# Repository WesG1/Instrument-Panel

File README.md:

# Instrument Panel
Description:
    Digital custom 65 mustang modern insturment panel. Uses six servo motors along with RGB LEDs to display gauge information. Controlled by an ESP32-s2. Motors and warning lights are interfaced through I2C protocall using a PCA9685 controller. Odometer and tripmeter are displayed on an I2C LCD. 
    
    Odo and trip values are stored in an EEPROM chip with a wear leveling algorithm. Odometer value is also stored in a second backup EEPROM. At startup the values of both EEPROMs are read, and if they are different the higher value is set as the current mileage. At shutdown the last stored value and current value for the mileage are compared and the current value is only stored if it is higher than the saved value.

    Each servo motor (execpt voltage) has a deticated sensor. The signals from the oil, temp, and fuel sensors are passed through a calibrated voltage divider to drop them to a level safe for the ESP32 to read. Speed and tach are a digital pulse and are passed through a logic shifter. Voltage is derived by an algorithm and read by a voltage divider from the dash power supply. Volts, oil, temp, and fuel have accompanying warning lights that turn red if the value goes out of a safe range, are off if the value is normal and the headlights are off, and white if the values is normal and the headlights are on. Temp has additionally will turn yellow if the value is too low.

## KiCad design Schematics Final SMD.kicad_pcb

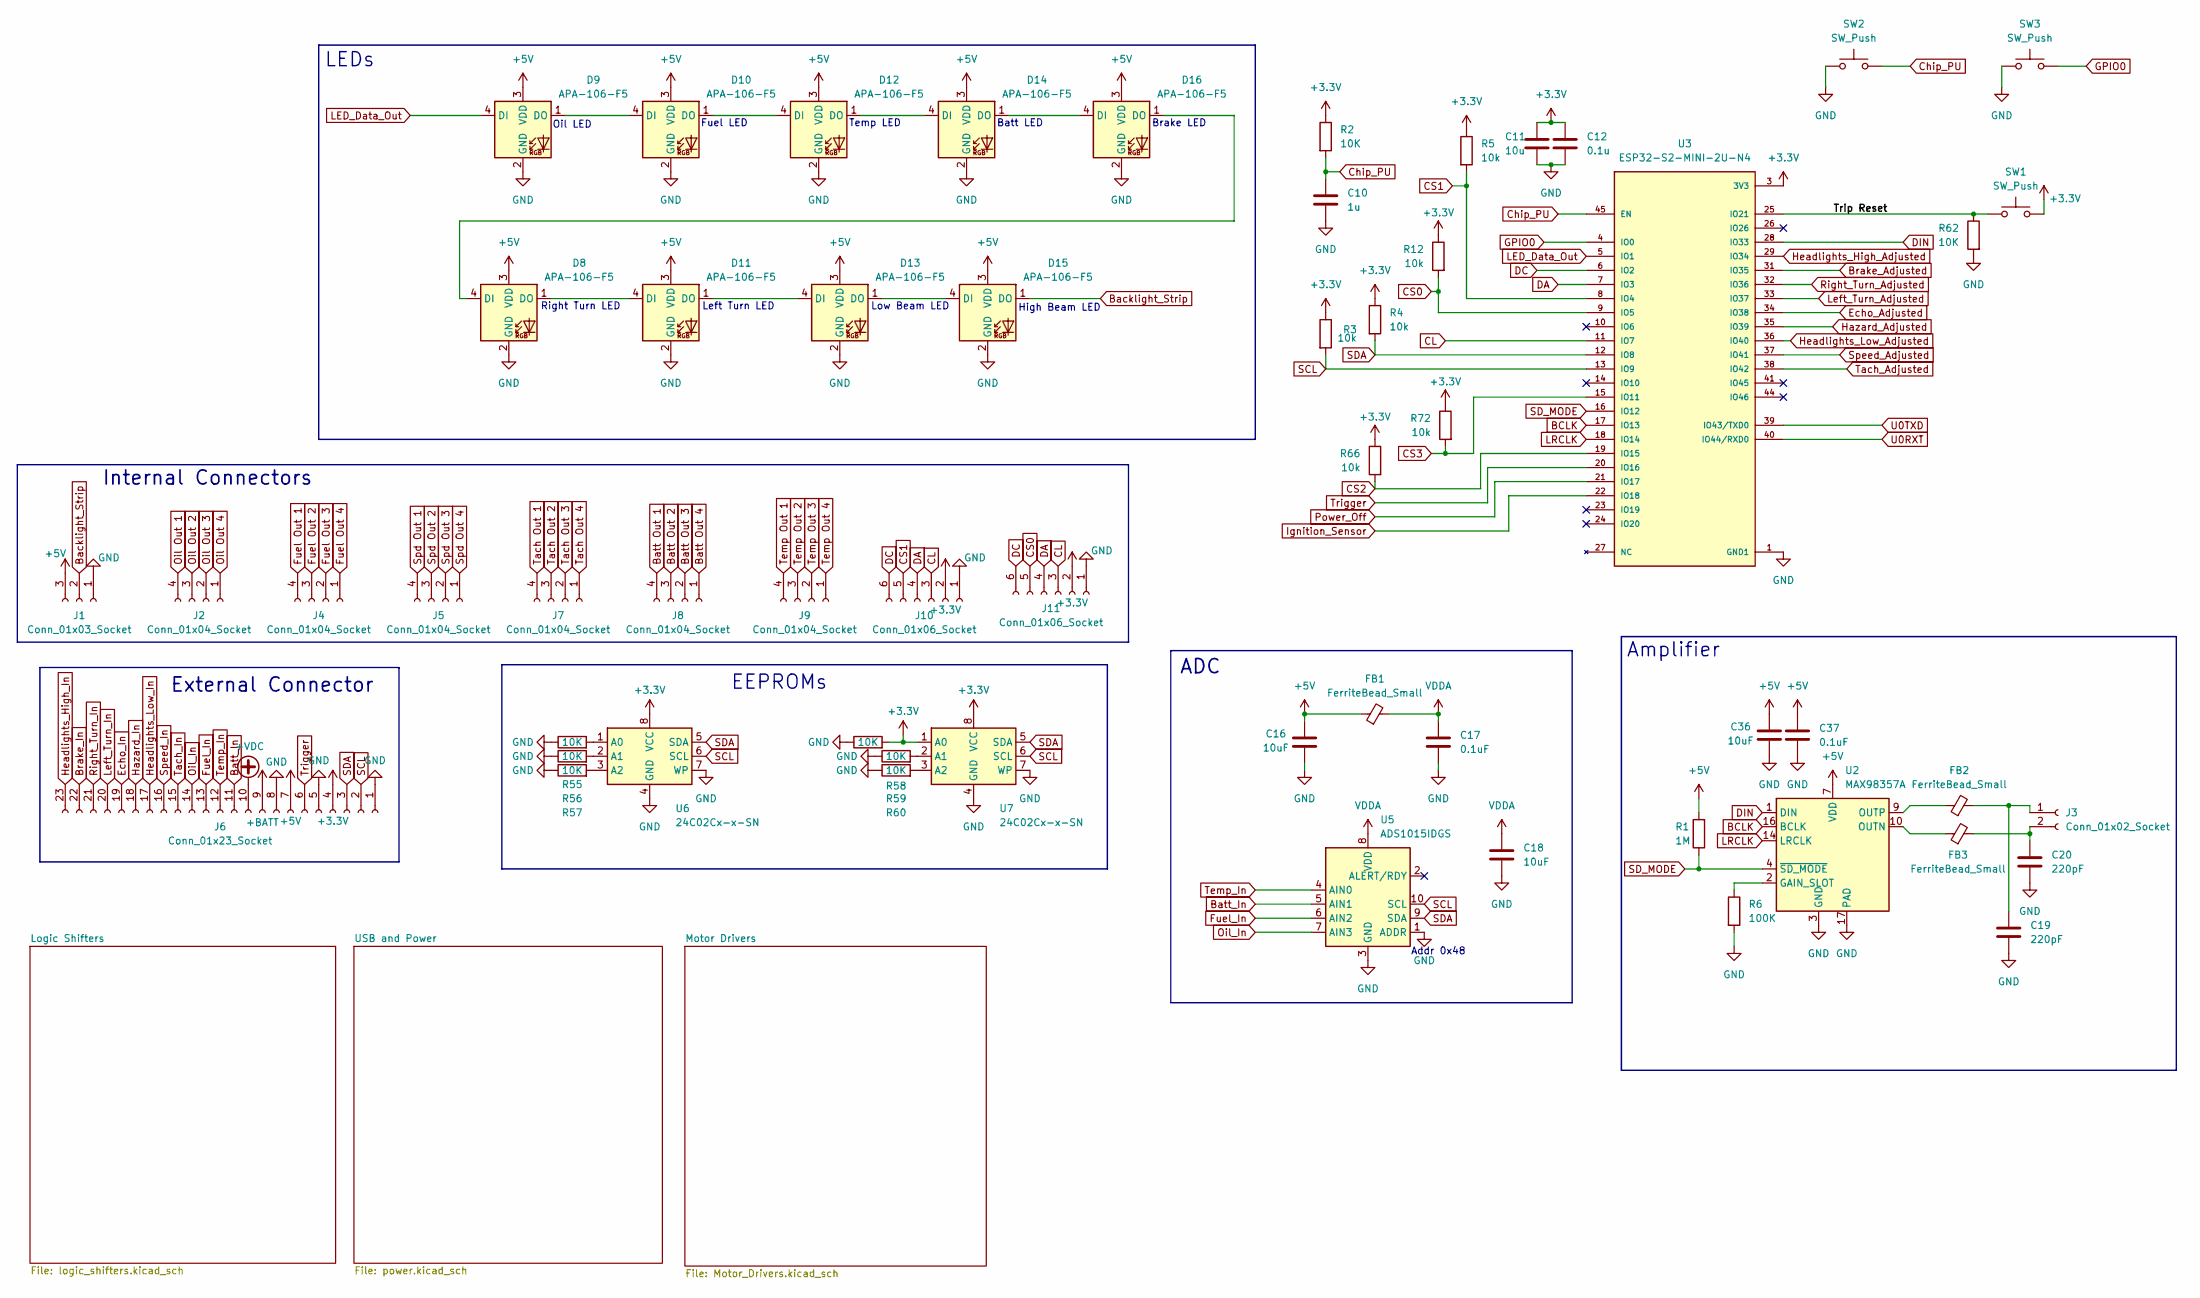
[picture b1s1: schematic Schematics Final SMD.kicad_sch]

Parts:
C10: 1u; C_Disc_D3.0mm_W1.6mm_P2.50mm
C11: 10u; C_Disc_D3.0mm_W1.6mm_P2.50mm
C12: 0.1u; C_Disc_D3.0mm_W1.6mm_P2.50mm
C16, C18, C36: 10uF; C_Disc_D3.0mm_W1.6mm_P2.50mm
C17, C37: 0.1uF; C_Disc_D3.0mm_W1.6mm_P2.50mm
C19, C20: 220pF; C_Disc_D3.0mm_W1.6mm_P2.50mm
D8, D9, D10, D11, D12, D13, D14, D15, D16: APA-106-F5; LED_D5.0mm-4_RGB
FB1, FB2, FB3: FerriteBead_Small; L_Axial_L5.0mm_D3.6mm_P10.00mm_Horizontal_Murata_BL01RN1A2A2
J1: Conn_01x03_Socket; Hirose_DF13-03P-1.25DSA_1x03_P1.25mm_Vertical
J2, J4, J5, J7, J8, J9: Conn_01x04_Socket
J3: Conn_01x02_Socket; Hirose_DF13-02P-1.25DSA_1x02_P1.25mm_Vertical
J6: Conn_01x23_Socket; Molex_SL_171971-0023_1x23_P2.54mm_Vertical
J10, J11: Conn_01x06_Socket; Hirose_DF13-06P-1.25DSA_1x06_P1.25mm_Vertical
R1: 1M; R_Axial_DIN0207_L6.3mm_D2.5mm_P10.16mm_Horizontal
R2, R55, R56, R57, R58, R59, R60, R62: 10K; R_Axial_DIN0207_L6.3mm_D2.5mm_P10.16mm_Horizontal
R3, R4, R5, R12, R66, R72: 10k; R_Axial_DIN0207_L6.3mm_D2.5mm_P10.16mm_Horizontal
R6: 100K; R_Axial_DIN0207_L6.3mm_D2.5mm_P10.16mm_Horizontal
SW1, SW2, SW3: SW_Push; SW_PUSH_6mm_H8mm
U2: MAX98357A; TQFN-16-1EP_3x3mm_P0.5mm_EP1.23x1.23mm
U3: ESP32-S2-MINI-2U-N4; XCVR_ESP32-S2-MINI-2U-N4; PARTREV v0.5
U5: ADS1015IDGS; TSSOP-10_3x3mm_P0.5mm
U6, U7: 24C02Cx-x-SN; DIP-8_W7.62mm

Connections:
+3.3V: C11.1, C12.1, J6.4, J10.2, J11.2, R2.1, R3.1, R4.1, R5.1, R12.1, R58.2, R66.1, R72.1, SW1.1, U3.3 (3V3), U6.8 (VCC), U7.1 (A0), U7.8 (VCC); also elsewhere on the board
+5V: C16.1, C36.1, C37.1, D8.3 (VDD), D9.3 (VDD), D10.3 (VDD), D11.3 (VDD), D12.3 (VDD), D13.3 (VDD), D14.3 (VDD), D15.3 (VDD), D16.3 (VDD), FB1.1, J1.3, J6.7, R1.2, U2.7 (VDD), U2.8 (VDD); also elsewhere on the board
+BATT: J6.9; also elsewhere on the board
+VDC: J6.10; also elsewhere on the board
/Trip Reset: R62.1, SW1.2, U3.25 (IO21)
BCLK: U2.16 (BCLK), U3.17 (IO13)
Backlight_Strip: D15.1 (DO), J1.2
Batt Out 1: J8.4; also elsewhere on the board
Batt Out 2: J8.3; also elsewhere on the board
Batt Out 3: J8.2; also elsewhere on the board
Batt Out 4: J8.1; also elsewhere on the board
Batt_In: J6.11, U5.5 (AIN1)
Brake_In: J6.22; also elsewhere on the board
CL: J10.3, J11.3, U3.11 (IO7); also elsewhere on the board
CS0: J11.5, R12.2, U3.9 (IO5)
CS1: J10.5, R5.2, U3.8 (IO4)
CS2: R66.2, U3.19 (IO15); also elsewhere on the board
CS3: R72.2, U3.15 (IO11); also elsewhere on the board
Chip_PU: C10.1, R2.2, SW2.2, U3.45 (EN); also elsewhere on the board
DA: J10.4, J11.4, U3.7 (IO3); also elsewhere on the board
DC: J10.6, J11.6, U3.6 (IO2)
DIN: U2.1 (DIN), U3.28 (IO33)
Echo_In: J6.19; also elsewhere on the board
Fuel Out 1: J4.4; also elsewhere on the board
Fuel Out 2: J4.3; also elsewhere on the board
Fuel Out 3: J4.2; also elsewhere on the board
Fuel Out 4: J4.1; also elsewhere on the board
Fuel_In: J6.13, U5.6 (AIN2)
GND: C10.2, C11.2, C12.2, C16.2, C17.2, C18.2, C19.2, C20.2, C36.2, C37.2, D8.2 (GND), D9.2 (GND), D10.2 (GND), D11.2 (GND), D12.2 (GND), D13.2 (GND), D14.2 (GND), D15.2 (GND), D16.2 (GND), J1.1, J6.1, J6.5, J6.8, J10.1, J11.1, R6.2, R55.1, R56.1, R57.1, R58.1, R59.1, R60.1, R62.2, SW2.1, SW3.1, U2.3 (GND), U2.11 (GND), U2.15 (GND), U2.17 (PAD), U3.1 (GND1), U3.2 (GND1__1), U3.30 (GND1__2), U3.42 (GND1__3), U3.43 (GND1__4), U3.46 (GND1__5), U3.47 (GND1__6), U3.48 (GND1__7), U3.49 (GND1__8), U3.50 (GND1__9), U3.51 (GND1__10), U3.52 (GND1__11), U3.53 (GND1__12), U3.54 (GND1__13), U3.55 (GND1__14), U3.56 (GND2), U3.57 (GND2__1), U3.58 (GND2__2), U3.59 (GND2__3), U3.60 (GND2__4), U3.61_1 (GND2__5), U3.61_2 (GND2__6), U3.61_3 (GND2__7), U3.61_4 (GND2__8), U3.61_5 (GND2__9), U3.61_6 (GND2__10), U3.61_7 (GND2__11), U3.61_8 (GND2__12), U3.61_9 (GND2__13), U3.62 (GND2__14), U3.63 (GND3), U3.64 (GND3__1), U3.65 (GND3__2), U5.1 (ADDR), U5.3 (GND), U6.4 (GND), U6.7 (WP), U7.4 (GND), U7.7 (WP); also elsewhere on the board
GPIO0: SW3.2, U3.4 (IO0); also elsewhere on the board
Hazard_In: J6.18; also elsewhere on the board
Headlights_High_In: J6.23; also elsewhere on the board
Headlights_Low_In: J6.17; also elsewhere on the board
LED_Data_Out: D9.4 (DI), U3.5 (IO1)
LRCLK: U2.14 (LRCLK), U3.18 (IO14)
Left_Turn_In: J6.20; also elsewhere on the board
unnamed: D9.1 (DO), D10.4 (DI)
unnamed: D10.1 (DO), D12.4 (DI)
unnamed: D8.1 (DO), D11.4 (DI)
unnamed: D11.1 (DO), D13.4 (DI)
unnamed: D12.1 (DO), D14.4 (DI)
unnamed: D13.1 (DO), D15.4 (DI)
unnamed: D14.1 (DO), D16.4 (DI)
unnamed: D8.4 (DI), D16.1 (DO)
unnamed: C19.1, FB2.2, J3.1
unnamed: C20.1, FB3.2, J3.2
unnamed: R6.1, U2.2 (GAIN_SLOT)
unnamed: FB3.1, U2.10 (OUTN)
unnamed: FB2.1, U2.9 (OUTP)
unnamed: R55.2, U6.1 (A0)
unnamed: R56.2, U6.2 (A1)
unnamed: R57.2, U6.3 (A2)
unnamed: R59.2, U7.2 (A1)
unnamed: R60.2, U7.3 (A2)
Oil Out 1: J2.4; also elsewhere on the board
Oil Out 2: J2.3; also elsewhere on the board
Oil Out 3: J2.2; also elsewhere on the board
Oil Out 4: J2.1; also elsewhere on the board
Oil_In: J6.14, U5.7 (AIN3)
Right_Turn_In: J6.21; also elsewhere on the board
SCL: J6.2, R3.2, U3.13 (IO9), U5.10 (SCL), U6.6 (SCL), U7.6 (SCL)
SDA: J6.3, R4.2, U3.12 (IO8), U5.9 (SDA), U6.5 (SDA), U7.5 (SDA)
SD_MODE: R1.1, U2.4 (~SD_MODE), U3.16 (IO12)
Spd Out 1: J5.4; also elsewhere on the board
Spd Out 2: J5.3; also elsewhere on the board
Spd Out 3: J5.2; also elsewhere on the board
Spd Out 4: J5.1; also elsewhere on the board
Speed_In: J6.16; also elsewhere on the board
Tach Out 1: J7.4; also elsewhere on the board
Tach Out 2: J7.3; also elsewhere on the board
Tach Out 3: J7.2; also elsewhere on the board
Tach Out 4: J7.1; also elsewhere on the board
Tach_In: J6.15; also elsewhere on the board
Temp Out 1: J9.4; also elsewhere on the board
Temp Out 2: J9.3; also elsewhere on the board
Temp Out 3: J9.2; also elsewhere on the board
Temp Out 4: J9.1; also elsewhere on the board
Temp_In: J6.12, U5.4 (AIN0)
Trigger: J6.6, U3.20 (IO16)
VDDA: C17.1, C18.1, FB1.2, U5.8 (VDD)

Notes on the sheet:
Batt LED
Low Beam LED
Brake LED
Amplifier
External Connector
Temp LED
Left Turn LED
ADC
High Beam LED
Addr 0x48
EEPROMs
Fuel LED
Internal Connectors
Oil LED
LEDs
Right Turn LED

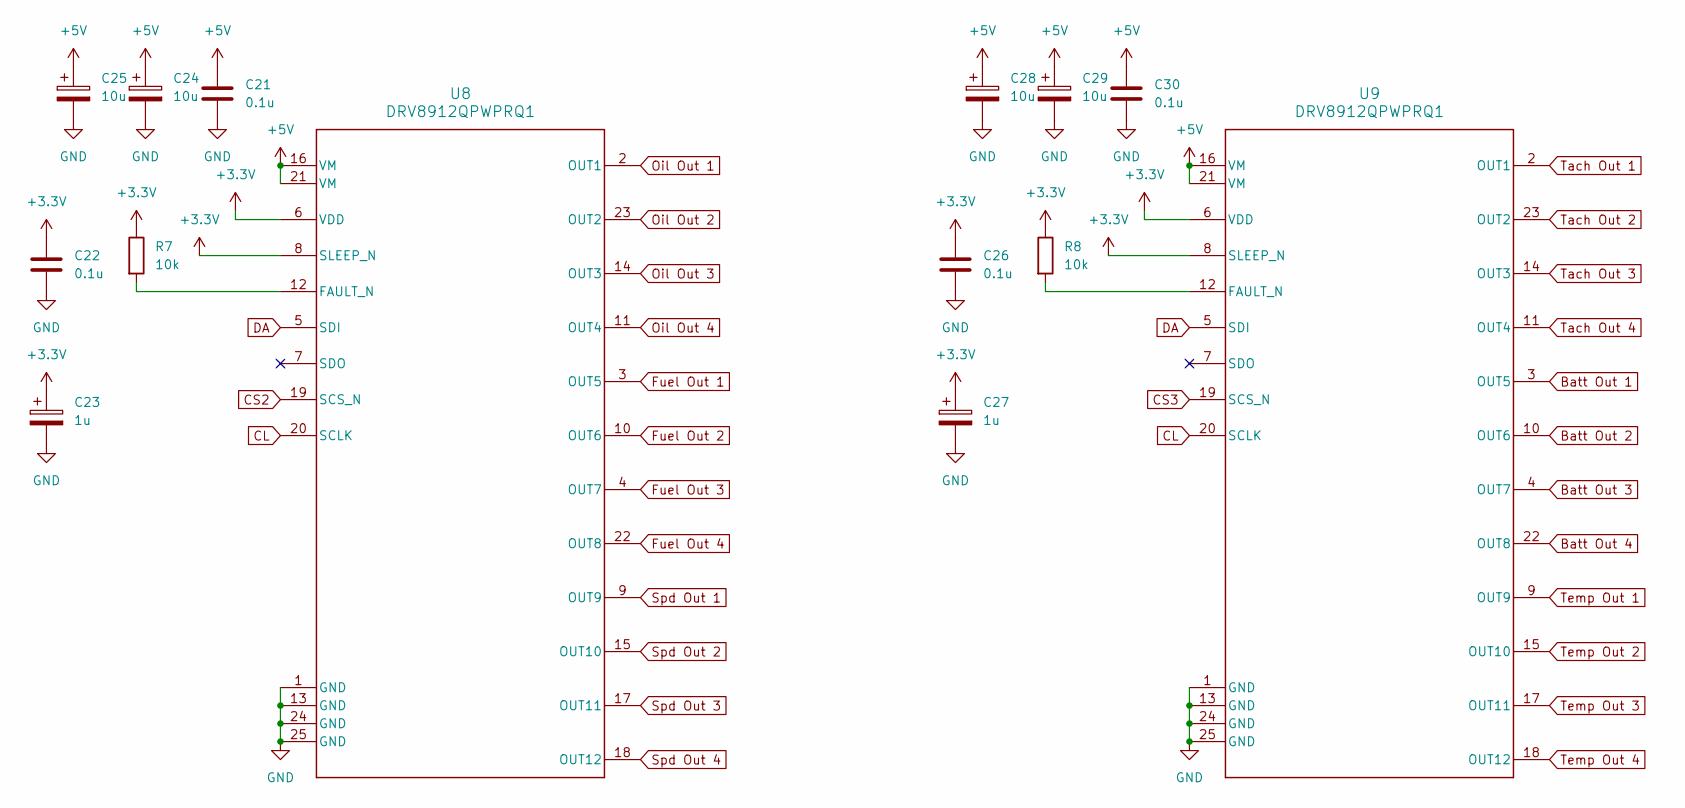
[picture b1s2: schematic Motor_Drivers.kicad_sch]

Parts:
C21, C22, C26, C30: 0.1u; C_1206_3216Metric
C23, C27: 1u; C_1206_3216Metric
C24, C25, C28, C29: 10u; C_1206_3216Metric
R7, R8: 10k; R_1206_3216Metric
U8, U9: DRV8912QPWPRQ1; PWP0024N_N

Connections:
+3.3V: C22.1, C23.1, C26.1, C27.1, R7.1, R8.1, U8.6 (VDD), U8.8 (SLEEP_N), U9.6 (VDD), U9.8 (SLEEP_N); also elsewhere on the board
+5V: C21.1, C24.1, C25.1, C28.1, C29.1, C30.1, U8.16 (VM), U8.21 (VM), U9.16 (VM), U9.21 (VM); also elsewhere on the board
Batt Out 1: U9.3 (OUT5); also elsewhere on the board
Batt Out 2: U9.10 (OUT6); also elsewhere on the board
Batt Out 3: U9.4 (OUT7); also elsewhere on the board
Batt Out 4: U9.22 (OUT8); also elsewhere on the board
CL: U8.20 (SCLK), U9.20 (SCLK); also elsewhere on the board
CS2: U8.19 (SCS_N); also elsewhere on the board
CS3: U9.19 (SCS_N); also elsewhere on the board
DA: U8.5 (SDI), U9.5 (SDI); also elsewhere on the board
Fuel Out 1: U8.3 (OUT5); also elsewhere on the board
Fuel Out 2: U8.10 (OUT6); also elsewhere on the board
Fuel Out 3: U8.4 (OUT7); also elsewhere on the board
Fuel Out 4: U8.22 (OUT8); also elsewhere on the board
GND: C21.2, C22.2, C23.2, C24.2, C25.2, C26.2, C27.2, C28.2, C29.2, C30.2, U8.1 (GND), U8.13 (GND), U8.24 (GND), U8.25 (GND), U9.1 (GND), U9.13 (GND), U9.24 (GND), U9.25 (GND); also elsewhere on the board
unnamed: R7.2, U8.12 (FAULT_N)
unnamed: R8.2, U9.12 (FAULT_N)
Oil Out 1: U8.2 (OUT1); also elsewhere on the board
Oil Out 2: U8.23 (OUT2); also elsewhere on the board
Oil Out 3: U8.14 (OUT3); also elsewhere on the board
Oil Out 4: U8.11 (OUT4); also elsewhere on the board
Spd Out 1: U8.9 (OUT9); also elsewhere on the board
Spd Out 2: U8.15 (OUT10); also elsewhere on the board
Spd Out 3: U8.17 (OUT11); also elsewhere on the board
Spd Out 4: U8.18 (OUT12); also elsewhere on the board
Tach Out 1: U9.2 (OUT1); also elsewhere on the board
Tach Out 2: U9.23 (OUT2); also elsewhere on the board
Tach Out 3: U9.14 (OUT3); also elsewhere on the board
Tach Out 4: U9.11 (OUT4); also elsewhere on the board
Temp Out 1: U9.9 (OUT9); also elsewhere on the board
Temp Out 2: U9.15 (OUT10); also elsewhere on the board
Temp Out 3: U9.17 (OUT11); also elsewhere on the board
Temp Out 4: U9.18 (OUT12); also elsewhere on the board

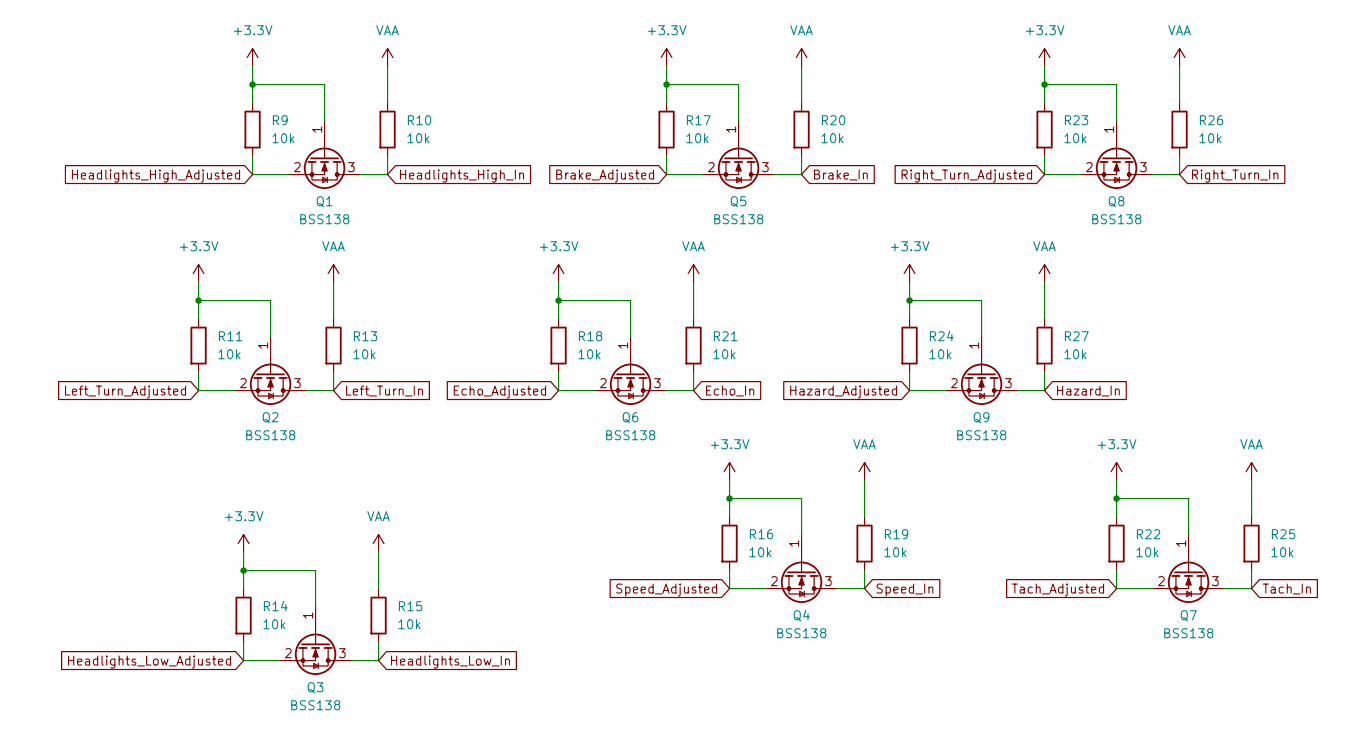
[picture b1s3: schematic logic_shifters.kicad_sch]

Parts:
Q1, Q2, Q3, Q4, Q5, Q6, Q7, Q8, Q9: BSS138; SOT-23
R9, R10, R11, R13, R14, R15, R16, R17, R18, R19, R20, R21, R22, R23, R24, R25, R26, R27: 10k; R_1206_3216Metric

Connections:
+3.3V: Q1.1 (G), Q2.1 (G), Q3.1 (G), Q4.1 (G), Q5.1 (G), Q6.1 (G), Q7.1 (G), Q8.1 (G), Q9.1 (G), R9.1, R11.1, R14.1, R16.1, R17.1, R18.1, R22.1, R23.1, R24.1; also elsewhere on the board
Brake_Adjusted: Q5.2 (S), R17.2
Brake_In: Q5.3 (D), R20.2; also elsewhere on the board
Echo_Adjusted: Q6.2 (S), R18.2
Echo_In: Q6.3 (D), R21.2; also elsewhere on the board
Hazard_Adjusted: Q9.2 (S), R24.2
Hazard_In: Q9.3 (D), R27.2; also elsewhere on the board
Headlights_High_Adjusted: Q1.2 (S), R9.2
Headlights_High_In: Q1.3 (D), R10.2; also elsewhere on the board
Headlights_Low_Adjusted: Q3.2 (S), R14.2
Headlights_Low_In: Q3.3 (D), R15.2; also elsewhere on the board
Left_Turn_Adjusted: Q2.2 (S), R11.2
Left_Turn_In: Q2.3 (D), R13.2; also elsewhere on the board
Right_Turn_Adjusted: Q8.2 (S), R23.2
Right_Turn_In: Q8.3 (D), R26.2; also elsewhere on the board
Speed_Adjusted: Q4.2 (S), R16.2
Speed_In: Q4.3 (D), R19.2; also elsewhere on the board
Tach_Adjusted: Q7.2 (S), R22.2
Tach_In: Q7.3 (D), R25.2; also elsewhere on the board
VAA: R10.1, R13.1, R15.1, R19.1, R20.1, R21.1, R25.1, R26.1, R27.1; also elsewhere on the board

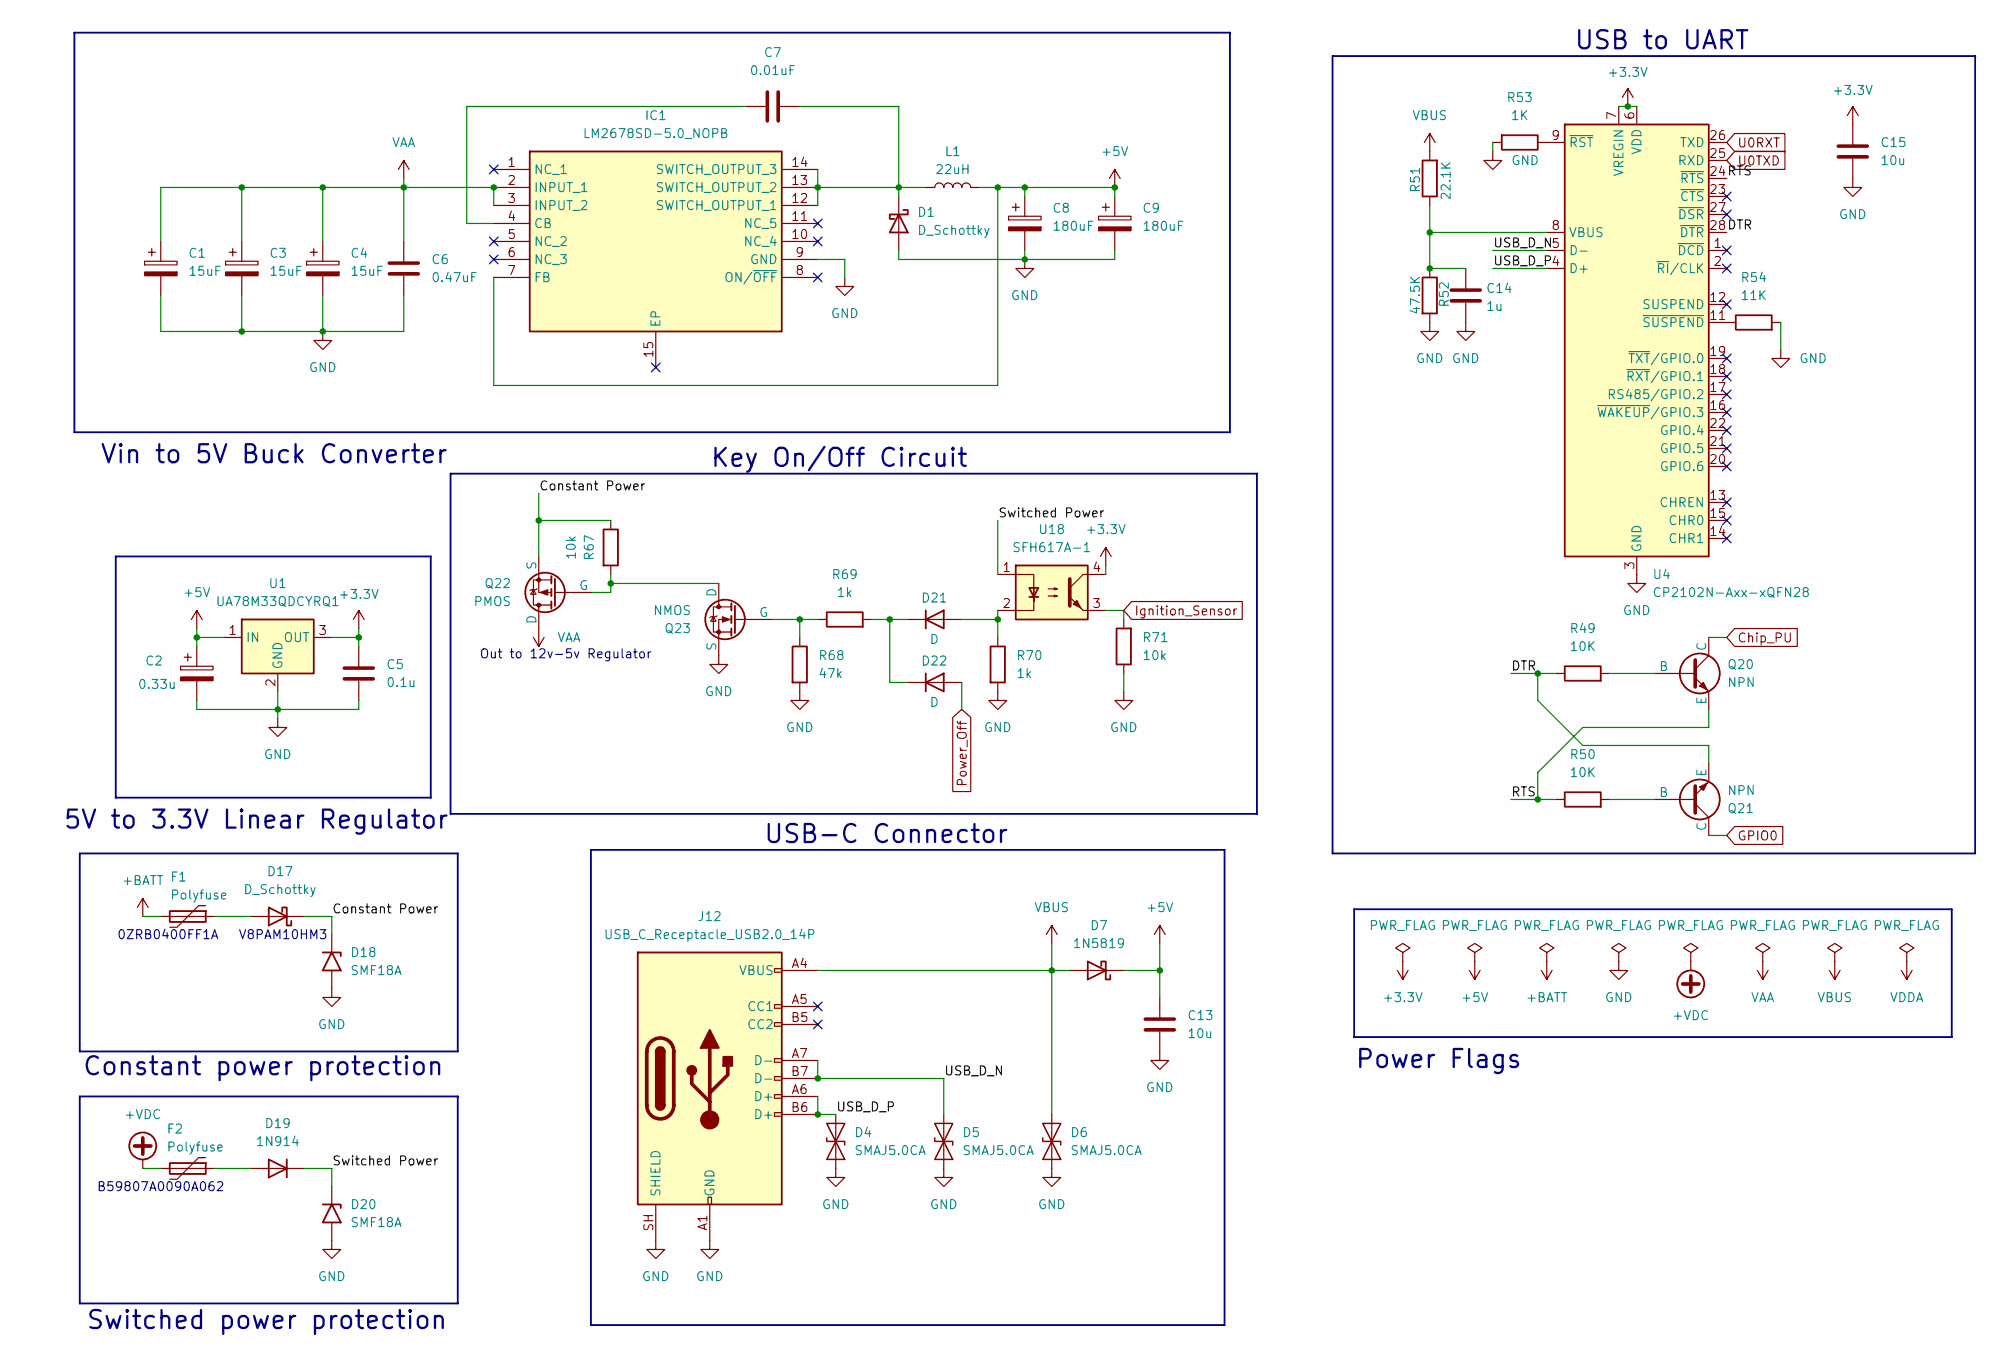
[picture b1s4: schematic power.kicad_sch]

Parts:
C1, C3, C4: 15uF; CP_Elec_6.3x5.4_Nichicon
C2: 0.33u; CP_Elec_6.3x5.4_Nichicon
C5: 0.1u; CP_Elec_6.3x5.4_Nichicon
C6: 0.47uF; CP_Elec_6.3x5.4_Nichicon
C7: 0.01uF; CP_Elec_6.3x5.4_Nichicon
C8, C9: 180uF; CP_Elec_6.3x5.4_Nichicon
C13, C15: 10u; C_1206_3216Metric
C14: 1u; C_1206_3216Metric
D1: D_Schottky; D_SMA
D4, D5, D6: SMAJ5.0CA; D_SMA
D7: 1N5819; D_SMA
D17: D_Schottky; Vishay_SMPA
D18, D20: SMF18A; D_SMF
D19: 1N914; D_SMA
D21, D22: D; D_SMA
F1, F2: Polyfuse; Fuse_1206_3216Metric
IC1: LM2678SD-5.0_NOPB; VSON-14-1EP_3x4.45mm_P0.65mm_EP1.6x4.2mm; Manufacturer_Part_Number LM2678SD-5.0/NOPB; Mouser Part Number 926-LM2678SD50NOPB
J12: USB_C_Receptacle_USB2.0_14P; USB_C_Receptacle_GCT_USB4085
L1: 22uH; L_Wuerth_XHMI-8080
Q20, Q21: NPN; SOT-23
Q22: PMOS; TO-220F-3_Horizontal_TabDown
Q23: NMOS; TO-220F-3_Horizontal_TabDown
R49, R50: 10K; R_1206_3216Metric
R51: 22.1K; R_1206_3216Metric
R52: 47.5K; R_1206_3216Metric
R53: 1K; R_1206_3216Metric
R54: 11K; R_1206_3216Metric
R67, R71: 10k; R_1206_3216Metric
R68: 47k; R_1206_3216Metric
R69, R70: 1k; R_1206_3216Metric
U1: UA78M33QDCYRQ1; SOT-223-3_TabPin2
U4: CP2102N-Axx-xQFN28; QFN-28-1EP_5x5mm_P0.5mm_EP3.35x3.35mm
U18: SFH617A-1; DIP-4_W7.62mm_SMDSocket_SmallPads

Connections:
+3.3V: C5.1, C15.1, U1.3 (OUT), U4.6 (VDD), U4.7 (VREGIN), U18.4; also elsewhere on the board
+5V: C2.1, C8.1, C9.1, C13.1, D7.1 (K), IC1.7 (FB), L1.2, U1.1 (IN); also elsewhere on the board
+BATT: F1.2; also elsewhere on the board
+VDC: F2.2; also elsewhere on the board
/USB and Power/Constant Power: D17.1 (K), D18.1 (A1), Q22.3 (S), R67.1
/USB and Power/DTR: Q21.3 (E), R49.1, U4.28 (~DTR)
/USB and Power/RTS: Q20.3 (E), R50.1, U4.24 (~RTS)
/USB and Power/Switched Power: D19.1 (K), D20.1 (A1), U18.1
/USB and Power/USB_D_N: D5.2 (A2), J12.A7 (D-), J12.B7 (D-), U4.5 (D-)
/USB and Power/USB_D_P: D4.2 (A2), J12.A6 (D+), J12.B6 (D+), U4.4 (D+)
Chip_PU: Q20.1 (C); also elsewhere on the board
GND: C1.2, C2.2, C3.2, C4.2, C5.2, C6.2, C8.2, C9.2, C13.2, C14.2, C15.2, D1.2 (A), D4.1 (A1), D5.1 (A1), D6.1 (A1), D18.2 (A2), D20.2 (A2), IC1.9 (GND), J12.A1 (GND), J12.A12 (GND), J12.B1 (GND), J12.B12 (GND), J12.SH (SHIELD), Q23.3 (S), R52.2, R53.2, R54.2, R68.2, R70.2, R71.1, U1.2 (GND), U4.3 (GND), U4.29 (GND); also elsewhere on the board
GPIO0: Q21.1 (C); also elsewhere on the board
Ignition_Sensor: R71.2, U18.3
unnamed: C7.2, D1.1 (K), IC1.12 (SWITCH_OUTPUT_1), IC1.13 (SWITCH_OUTPUT_2), IC1.14 (SWITCH_OUTPUT_3), L1.1
unnamed: D17.2 (A), F1.1
unnamed: D19.2 (A), F2.1
unnamed: D21.2 (A), R70.1, U18.2
unnamed: D21.1 (K), D22.1 (K), R69.2
unnamed: C7.1, IC1.4 (CB)
unnamed: Q20.2 (B), R49.2
unnamed: Q21.2 (B), R50.2
unnamed: Q22.2 (G), Q23.1 (D), R67.2
unnamed: Q23.2 (G), R68.1, R69.1
unnamed: C14.1, R51.1, R52.1, U4.8 (VBUS)
unnamed: R53.1, U4.9 (~RST)
unnamed: R54.1, U4.11 (~SUSPEND)
Power_Off: D22.2 (A)
U0RXT: U4.26 (TXD)
U0TXD: U4.25 (RXD)
VAA: C1.1, C3.1, C4.1, C6.1, IC1.2 (INPUT_1), IC1.3 (INPUT_2), Q22.1 (D); also elsewhere on the board
VBUS: D6.2 (A2), D7.2 (A), J12.A4 (VBUS), J12.A9 (VBUS), J12.B4 (VBUS), J12.B9 (VBUS), R51.2

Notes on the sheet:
Power Flags
USB to UART
5V to 3.3V Linear Regulator
Out to 12v-5v Regulator
Switched power protection
V8PAM10HM3
0ZRB0400FF1A
Constant power protection
USB-C Connector
Vin to 5V Buck Converter
Key On/Off Circuit
B59807A0090A062

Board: 2 copper layers, 143 parts (1 on the bottom side), 108 nets, no tracks yet.

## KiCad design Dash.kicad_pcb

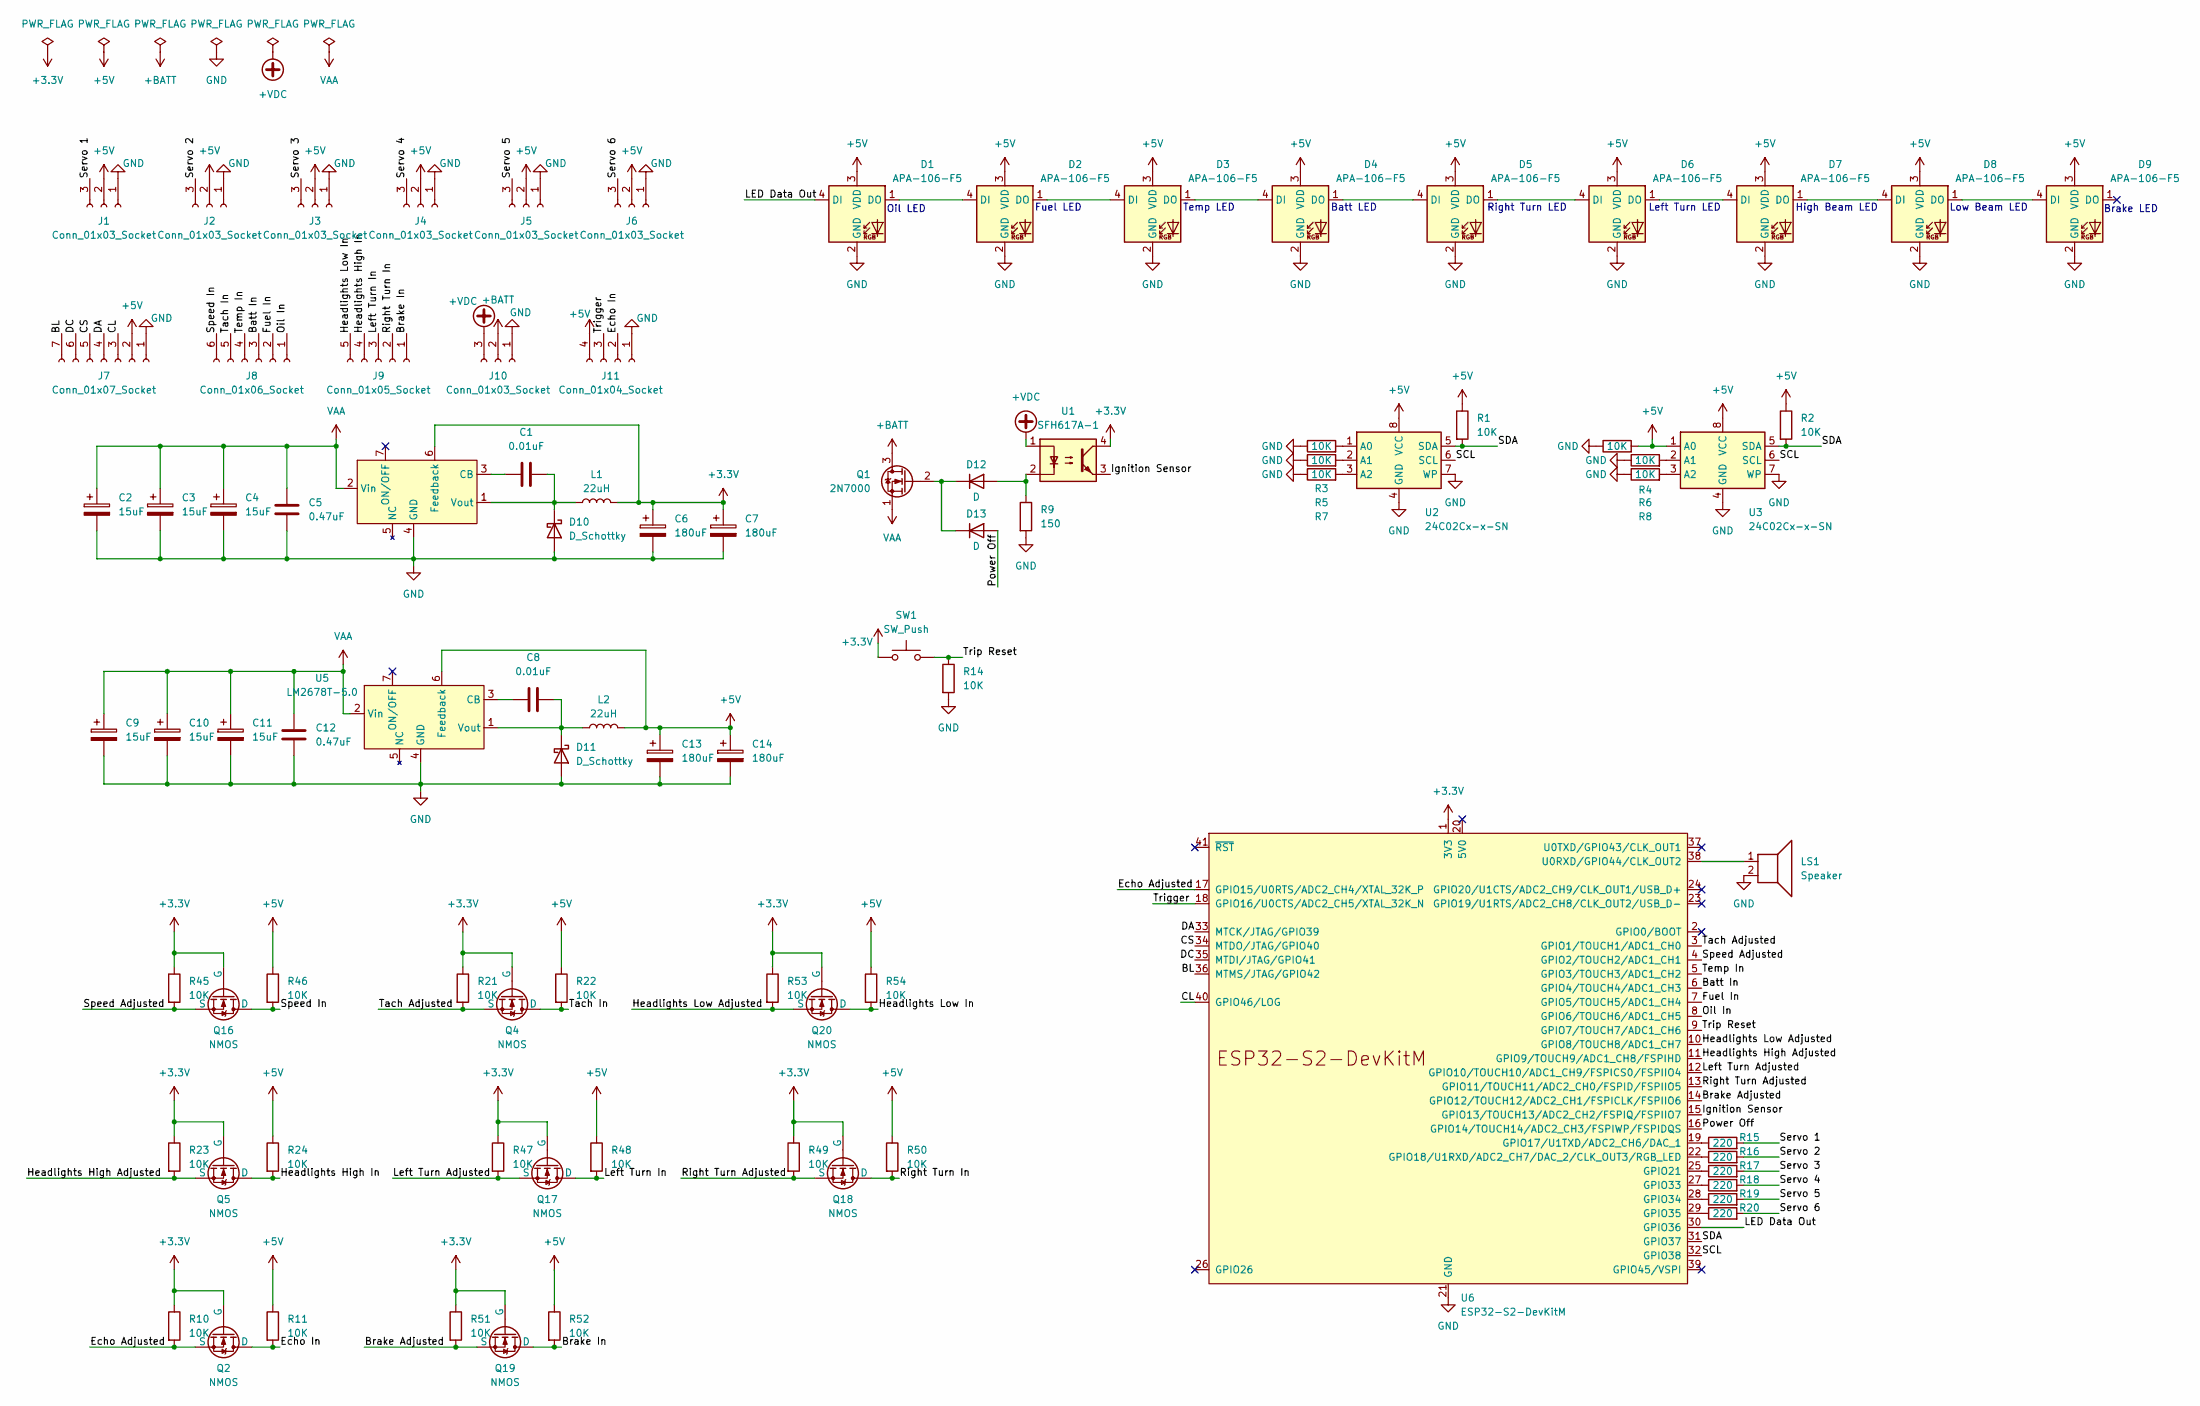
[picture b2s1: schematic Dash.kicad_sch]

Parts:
C1, C8: 0.01uF; C_Disc_D3.0mm_W1.6mm_P2.50mm
C2, C3, C4, C9, C10, C11: 15uF; CP_Radial_D5.0mm_P2.50mm
C5, C12: 0.47uF; C_Disc_D3.0mm_W1.6mm_P2.50mm
C6, C7, C13, C14: 180uF; CP_Radial_D5.0mm_P2.50mm
D1, D2, D3, D4, D5, D6, D7, D8, D9: APA-106-F5; LED_D5.0mm-4_RGB
D10, D11: D_Schottky; D_A-405_P7.62mm_Horizontal
D12, D13: D; D_A-405_P7.62mm_Horizontal
J1, J2, J3, J4, J5, J6, J10: Conn_01x03_Socket; Molex_KK-396_A-41791-0003_1x03_P3.96mm_Vertical
J7: Conn_01x07_Socket; Molex_KK-396_5273-07A_1x07_P3.96mm_Vertical
J8: Conn_01x06_Socket; Molex_KK-396_5273-06A_1x06_P3.96mm_Vertical
J9: Conn_01x05_Socket; Molex_KK-396_5273-05A_1x05_P3.96mm_Vertical
J11: Conn_01x04_Socket; Molex_KK-396_5273-04A_1x04_P3.96mm_Vertical
L1, L2: 22uH; L_Radial_D9.5mm_P5.00mm_Fastron_07HVP
LS1: Speaker; Molex_KK-396_5273-02A_1x02_P3.96mm_Vertical
Q1: 2N7000; TO-92_Inline
Q2, Q4, Q5, Q16, Q17, Q18, Q19, Q20: NMOS; TO-92_Inline
R1, R2, R3, R4, R5, R6, R7, R8, R10, R11, R14, R21, R22, R23, R24, R45, R46, R47, R48, R49, R50, R51, R52, R53, R54: 10K; R_Axial_DIN0207_L6.3mm_D2.5mm_P10.16mm_Horizontal
R9: 150; R_Axial_DIN0207_L6.3mm_D2.5mm_P10.16mm_Horizontal
R15, R16, R17, R18, R19, R20: 220; R_Axial_DIN0207_L6.3mm_D2.5mm_P10.16mm_Horizontal
SW1: SW_Push; SW_PUSH_6mm_H8mm
U1: SFH617A-1; DIP-4_W7.62mm
U2, U3: 24C02Cx-x-SN; SOIC-8_3.9x4.9mm_P1.27mm
U4: LM2678T-3.3; TO-220-7_P2.54x3.7mm_StaggerOdd_Lead3.8mm_Vertical
U5: LM2678T-5.0; TO-220-7_P2.54x3.7mm_StaggerOdd_Lead3.8mm_Vertical
U6: ESP32-S2-DevKitM

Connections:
+3.3V: C6.1, C7.1, L1.2, Q2.2 (G), Q4.2 (G), Q5.2 (G), Q16.2 (G), Q17.2 (G), Q18.2 (G), Q19.2 (G), Q20.2 (G), R10.1, R21.1, R23.1, R45.1, R47.1, R49.1, R51.1, R53.1, SW1.1, U1.4, U4.6 (Feedback), U6.1 (3V3)
+5V: C13.1, C14.1, D1.3 (VDD), D2.3 (VDD), D3.3 (VDD), D4.3 (VDD), D5.3 (VDD), D6.3 (VDD), D7.3 (VDD), D8.3 (VDD), D9.3 (VDD), J1.2, J2.2, J3.2, J4.2, J5.2, J6.2, J7.2, J11.4, L2.2, R1.1, R2.1, R4.2, R11.1, R22.1, R24.1, R46.1, R48.1, R50.1, R52.1, R54.1, U2.8 (VCC), U3.1 (A0), U3.8 (VCC), U5.6 (Feedback)
+BATT: J10.2, Q1.3 (D)
+VDC: J10.3, U1.1
/BL: J7.7, U6.36 (MTMS/JTAG/GPIO42)
/Batt In: J8.3, U6.6 (GPIO4/TOUCH4/ADC1_CH3)
/Brake Adjusted: Q19.3 (S), R51.2, U6.14 (GPIO12/TOUCH12/ADC2_CH1/FSPICLK/FSPIIO6)
/Brake In: J9.1, Q19.1 (D), R52.2
/CL: J7.3, U6.40 (GPIO46/LOG)
/CS: J7.5, U6.34 (MTDO/JTAG/GPIO40)
/DA: J7.4, U6.33 (MTCK/JTAG/GPIO39)
/DC: J7.6, U6.35 (MTDI/JTAG/GPIO41)
/Echo Adjusted: Q2.3 (S), R10.2, U6.17 (GPIO15/U0RTS/ADC2_CH4/XTAL_32K_P)
/Echo In: J11.2, Q2.1 (D), R11.2
/Fuel In: J8.2, U6.7 (GPIO5/TOUCH5/ADC1_CH4)
/Headlights High Adjusted: Q5.3 (S), R23.2, U6.11 (GPIO9/TOUCH9/ADC1_CH8/FSPIHD)
/Headlights High In: J9.4, Q5.1 (D), R24.2
/Headlights Low Adjusted: Q20.3 (S), R53.2, U6.10 (GPIO8/TOUCH8/ADC1_CH7)
/Headlights Low In: J9.5, Q20.1 (D), R54.2
/Ignition Sensor: U1.3, U6.15 (GPIO13/TOUCH13/ADC2_CH2/FSPIQ/FSPIIO7)
/LED Data Out: D1.4 (DI), U6.30 (GPIO36)
/Left Turn Adjusted: Q17.3 (S), R47.2, U6.12 (GPIO10/TOUCH10/ADC1_CH9/FSPICS0/FSPIIO4)
/Left Turn In: J9.3, Q17.1 (D), R48.2
/Oil In: J8.1, U6.8 (GPIO6/TOUCH6/ADC1_CH5)
/Power Off: D13.2 (A), U6.16 (GPIO14/TOUCH14/ADC2_CH3/FSPIWP/FSPIDQS)
/Right Turn Adjusted: Q18.3 (S), R49.2, U6.13 (GPIO11/TOUCH11/ADC2_CH0/FSPID/FSPIIO5)
/Right Turn In: J9.2, Q18.1 (D), R50.2
/SCL: U2.6 (SCL), U3.6 (SCL), U6.32 (GPIO38)
/SDA: R1.2, R2.2, U2.5 (SDA), U3.5 (SDA), U6.31 (GPIO37)
/Servo 1: J1.3, R15.2
/Servo 2: J2.3, R16.2
/Servo 3: J3.3, R17.2
/Servo 4: J4.3, R18.2
/Servo 5: J5.3, R19.2
/Servo 6: J6.3, R20.2
/Speed Adjusted: Q16.3 (S), R45.2, U6.4 (GPIO2/TOUCH2/ADC1_CH1)
/Speed In: J8.6, Q16.1 (D), R46.2
/Tach Adjusted: Q4.3 (S), R21.2, U6.3 (GPIO1/TOUCH1/ADC1_CH0)
/Tach In: J8.5, Q4.1 (D), R22.2
/Temp In: J8.4, U6.5 (GPIO3/TOUCH3/ADC1_CH2)
/Trigger: J11.3, U6.18 (GPIO16/U0CTS/ADC2_CH5/XTAL_32K_N)
/Trip Reset: R14.1, SW1.2, U6.9 (GPIO7/TOUCH7/ADC1_CH6)
GND: C2.2, C3.2, C4.2, C5.2, C6.2, C7.2, C9.2, C10.2, C11.2, C12.2, C13.2, C14.2, D1.2 (GND), D2.2 (GND), D3.2 (GND), D4.2 (GND), D5.2 (GND), D6.2 (GND), D7.2 (GND), D8.2 (GND), D9.2 (GND), D10.2 (A), D11.2 (A), J1.1, J2.1, J3.1, J4.1, J5.1, J6.1, J7.1, J10.1, J11.1, LS1.2, R3.1, R4.1, R5.1, R6.1, R7.1, R8.1, R9.2, R14.2, U2.4 (GND), U2.7 (WP), U3.4 (GND), U3.7 (WP), U4.4 (GND), U5.4 (GND), U6.21 (GND), U6.42 (GND)
unnamed: D1.1 (DO), D2.4 (DI)
unnamed: D2.1 (DO), D3.4 (DI)
unnamed: D3.1 (DO), D4.4 (DI)
unnamed: D4.1 (DO), D5.4 (DI)
unnamed: D5.1 (DO), D6.4 (DI)
unnamed: D6.1 (DO), D7.4 (DI)
unnamed: D7.1 (DO), D8.4 (DI)
unnamed: D8.1 (DO), D9.4 (DI)
unnamed: C1.2, D10.1 (K), L1.1, U4.1 (Vout)
unnamed: C8.2, D11.1 (K), L2.1, U5.1 (Vout)
unnamed: D12.2 (A), R9.1, U1.2
unnamed: D12.1 (K), D13.1 (K), Q1.2 (G)
unnamed: R3.2, U2.1 (A0)
unnamed: R5.2, U2.2 (A1)
unnamed: R7.2, U2.3 (A2)
unnamed: R6.2, U3.2 (A1)
unnamed: R8.2, U3.3 (A2)
unnamed: C1.1, U4.3 (CB)
unnamed: C8.1, U5.3 (CB)
unnamed: R15.1, U6.19 (GPIO17/U1TXD/ADC2_CH6/DAC_1)
unnamed: R16.1, U6.22 (GPIO18/U1RXD/ADC2_CH7/DAC_2/CLK_OUT3/RG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)
unnamed: R17.1, U6.25 (GPIO21)
unnamed: R18.1, U6.27 (GPIO33)
unnamed: R19.1, U6.28 (GPIO34)
unnamed: R20.1, U6.29 (GPIO35)
unnamed: LS1.1, U6.38 (U0RXD/GPIO44/CLK_OUT2)
VAA: C2.1, C3.1, C4.1, C5.1, C9.1, C10.1, C11.1, C12.1, Q1.1 (S), U4.2 (Vin), U5.2 (Vin)

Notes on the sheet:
Low Beam LED
High Beam LED
Fuel LED
Oil LED
Temp LED
Batt LED
Left Turn LED
Right Turn LED
Brake LED
